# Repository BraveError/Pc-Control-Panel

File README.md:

# Pc-Control-Panel
A hackpad for Hack Club Blueprint. Has 6 shortcut keys, an OLED display, and a volume knob with leds to show volume.

# Cad

The design includes 3 3D printed parts: A back piece that supports the PCB at a 45 degree angle, a front panel with cutouts, and a small spacer to support the OLED display. 
Modeled in Fusion.

# PCB

Notable features include:
<ul>
  <li>Larger traces for 5v and 3v3 power rails</li>
  <li>Large ground plane with minimal via usage</li>
</ul>
Made in KiCad.

# Firmware (WIP)
Hackpad uses KMK firmware. Currently, code uses switches to act as a small keyboard. More features (keyboard shortcuts, volume control, oled clock) are planned once board is available for testing.

# Bill of Materials
<ul>
  <li>1x PCB from PCBWay</li>
  <li>1x XIAO RP2040</li>
  <li>1x 0.91 in OLED</li>
  <li>1x EC11 Encoder</li>
  <li>6x MX-Style switches</li>
  <li>6x Blank DSA keycaps</li>
  <li>10x SK6812 MINI-E LEDs</li>
</ul>
All other parts (3d prints, screws) will be self-provided.

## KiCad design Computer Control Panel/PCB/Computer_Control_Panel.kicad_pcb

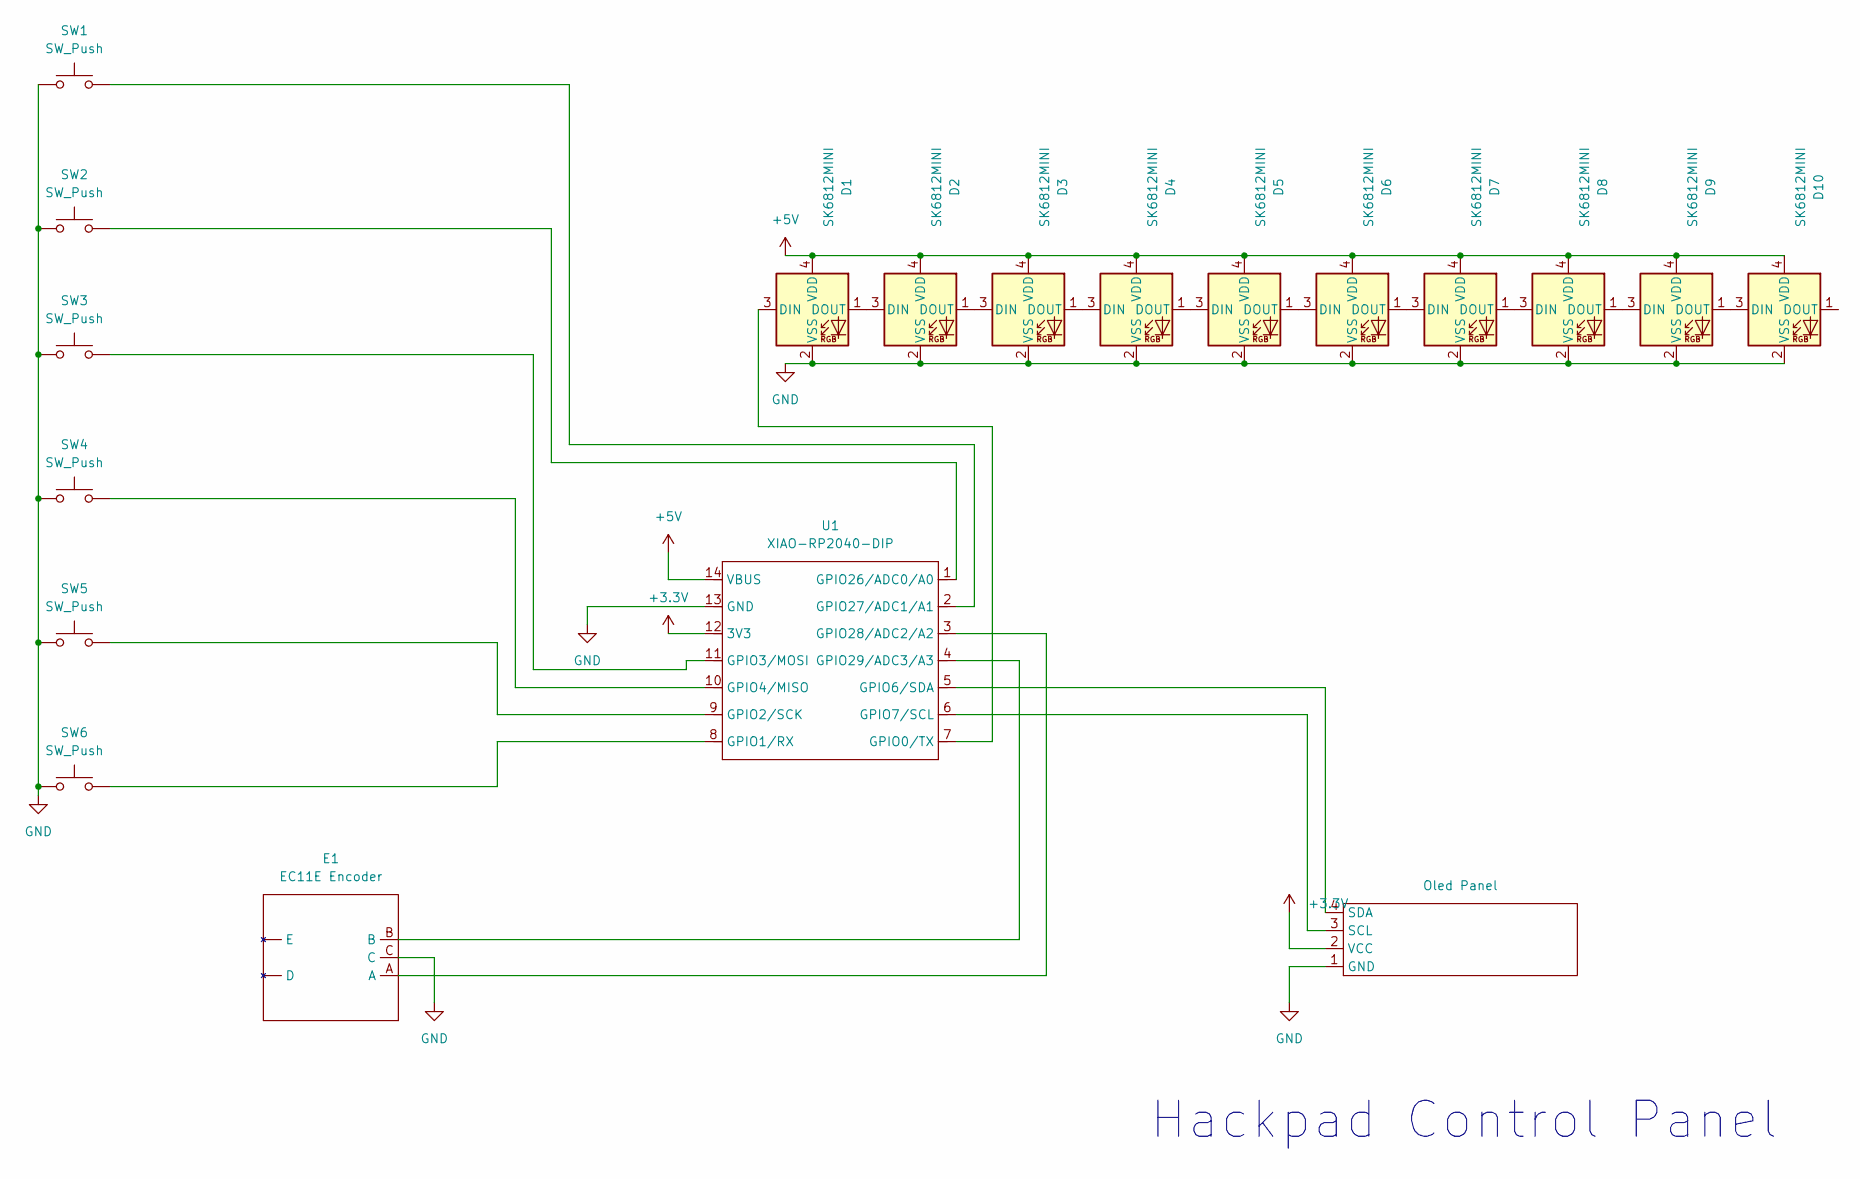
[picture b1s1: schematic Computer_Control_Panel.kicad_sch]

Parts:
1: Oled Panel; SSD1306-0.91-OLED-4pin-128x32
D1, D2, D3, D4, D5, D6, D7, D8, D9, D10: SK6812MINI; LED_SK6812MINI_PLCC4_3.5x3.5mm_P1.75mm
E1: EC11E Encoder; RotaryEncoder_Alps_EC11E_Vertical_H20mm
SW1, SW2, SW3, SW4, SW5, SW6: SW_Push; SW_Cherry_MX_1.00u_PCB
U1: XIAO-RP2040-DIP

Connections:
+3.3V: 1.2 (VCC), U1.12 (3V3)
+5V: D1.4 (VDD), D2.4 (VDD), D3.4 (VDD), D4.4 (VDD), D5.4 (VDD), D6.4 (VDD), D7.4 (VDD), D8.4 (VDD), D9.4 (VDD), D10.4 (VDD), U1.14 (VBUS)
GND: 1.1 (GND), D1.2 (VSS), D2.2 (VSS), D3.2 (VSS), D4.2 (VSS), D5.2 (VSS), D6.2 (VSS), D7.2 (VSS), D8.2 (VSS), D9.2 (VSS), D10.2 (VSS), E1.C, SW1.1, SW2.1, SW3.1, SW4.1, SW5.1, SW6.1, U1.13 (GND)
unnamed: 1.3 (SCL), U1.6 (GPIO7/SCL)
unnamed: 1.4 (SDA), U1.5 (GPIO6/SDA)
unnamed: D1.3 (DIN), U1.7 (GPIO0/TX)
unnamed: D1.1 (DOUT), D2.3 (DIN)
unnamed: D2.1 (DOUT), D3.3 (DIN)
unnamed: D3.1 (DOUT), D4.3 (DIN)
unnamed: D4.1 (DOUT), D5.3 (DIN)
unnamed: D5.1 (DOUT), D6.3 (DIN)
unnamed: D6.1 (DOUT), D7.3 (DIN)
unnamed: D7.1 (DOUT), D8.3 (DIN)
unnamed: D8.1 (DOUT), D9.3 (DIN)
unnamed: D9.1 (DOUT), D10.3 (DIN)
unnamed: SW6.2, U1.8 (GPIO1/RX)
unnamed: SW5.2, U1.9 (GPIO2/SCK)
unnamed: SW3.2, U1.11 (GPIO3/MOSI)
unnamed: SW4.2, U1.10 (GPIO4/MISO)
unnamed: SW2.2, U1.1 (GPIO26/ADC0/A0)
unnamed: SW1.2, U1.2 (GPIO27/ADC1/A1)
unnamed: E1.A, U1.3 (GPIO28/ADC2/A2)
unnamed: E1.B, U1.4 (GPIO29/ADC3/A3)

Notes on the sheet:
Hackpad Control Panel

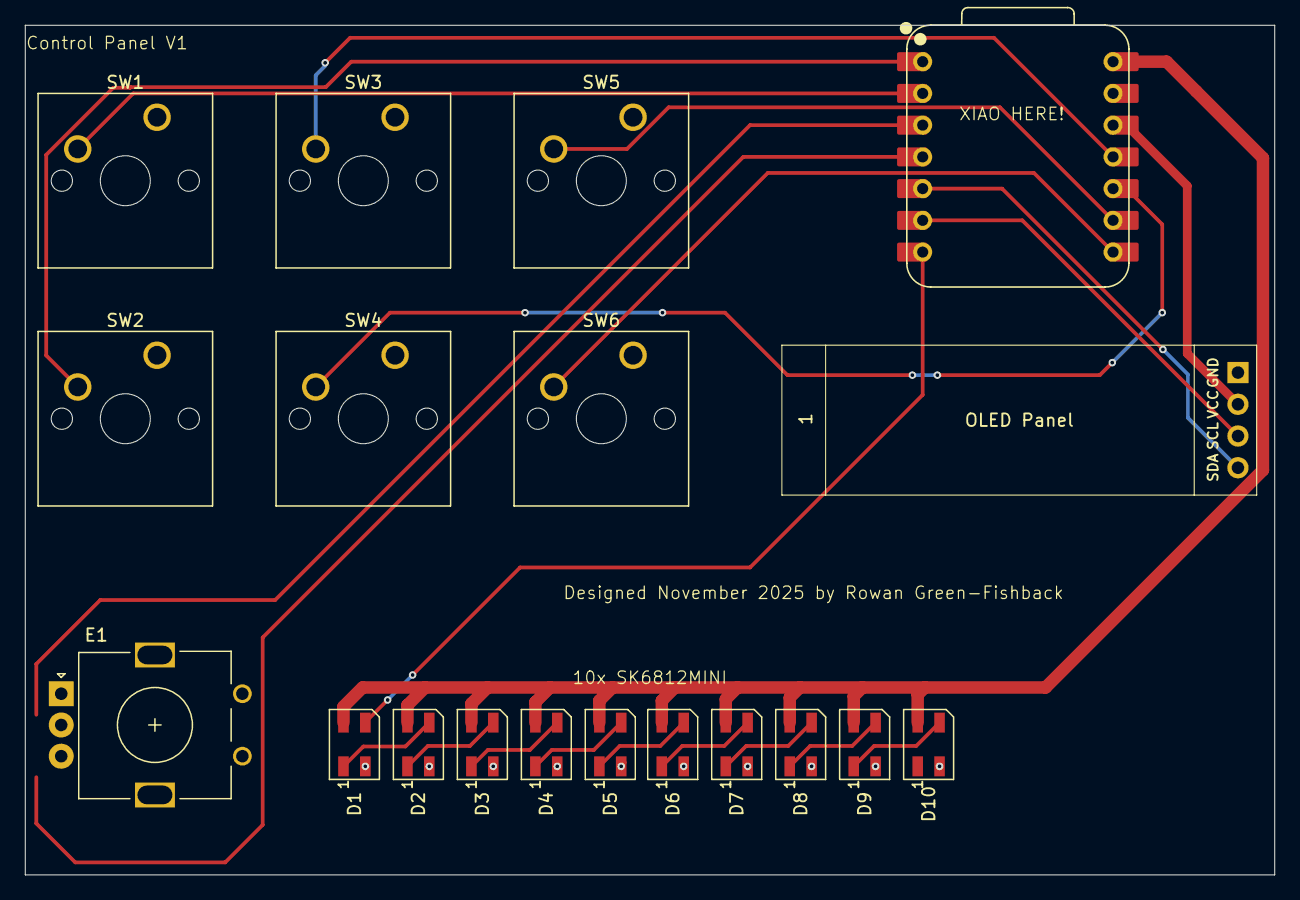
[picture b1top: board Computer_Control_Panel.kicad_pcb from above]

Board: 2 copper layers, 100.0 x 68.0 mm, 19 parts (0 on the bottom side), 23 nets.

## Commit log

2025-11-29 added assets
2025-11-29 rename
